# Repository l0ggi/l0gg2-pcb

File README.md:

# l0gg2-pcb
2nd gen PCB for l0ggi project

## Project
The idea behind l0ggi is to develop an open source hardware platform to log data, mainly environmental values like temperature and humidity, further also atmospheric pressure, co2, nox etc.
After a quick and dirty pcb with l0gg1 (not working out of the box) the logg2 pcb fixes all bugs of the older iteration and implements the possibility to operate the pcb via battery and accus.
l0gg2 does not feature a usb interface and is designed to be used with the open source tasmota sensors firmware (https://tasmota.github.io/docs/). As the firmware offers the possibility for OTA updates out of the box the usb interface was removed.
The type-c connector of the older iteration is replaced with a overall cheaper micro-usb. The data-lines are not terminated and not used. 

## Ordering
The gerber files are available and proven to work. 
Pick and place files are still in progress

## Firmware
While Tasmota works, the Bosch BME temperature, humidity and atmospheric pressure sensor which is intended to used with the pcb works with Tasmota-Sensors. 

### Flashing
A standard 3.3V FTDI cable can be used, but TX/RX needs to be inverted on the cable. This bug is known and will be fixed in l0gg2.1
Connect USB for power and the adapted FTDI cable to l0gg2. Press PRG (below ESP on the right) and hold and trigger RESET (below ESP on the left). Hold PRG and start flashing via the web tool of tasmota. 

### Configuration (Bosch Sensor, default)
Port | Function
---|---
GPIO0|Button 1
GPIO1|Serial TX
GPIO2|I2C SDA
GPIO3|Serial RX
GPIO4|Button 2
GPIO5|Button 3
GPIO6|
GPIO7|
GPIO8|
GPIO9|
GPIO10|
GPIO11|
GPIO12|
GPIO13|
GPIO14|I2C SCL
GPIO15|
GPIO16|
GPIO17|ADC In

### Configuration (AM2301, soldered to I2C header)
Port | Function
---|---
GPIO0|
GPIO1|
GPIO2|AM2301
GPIO3|
GPIO4|
GPIO5|
GPIO6|
GPIO7|
GPIO8|
GPIO9|
GPIO10|
GPIO11|
GPIO12|
GPIO13|
GPIO14|
GPIO15|
GPIO16|
GPIO17|

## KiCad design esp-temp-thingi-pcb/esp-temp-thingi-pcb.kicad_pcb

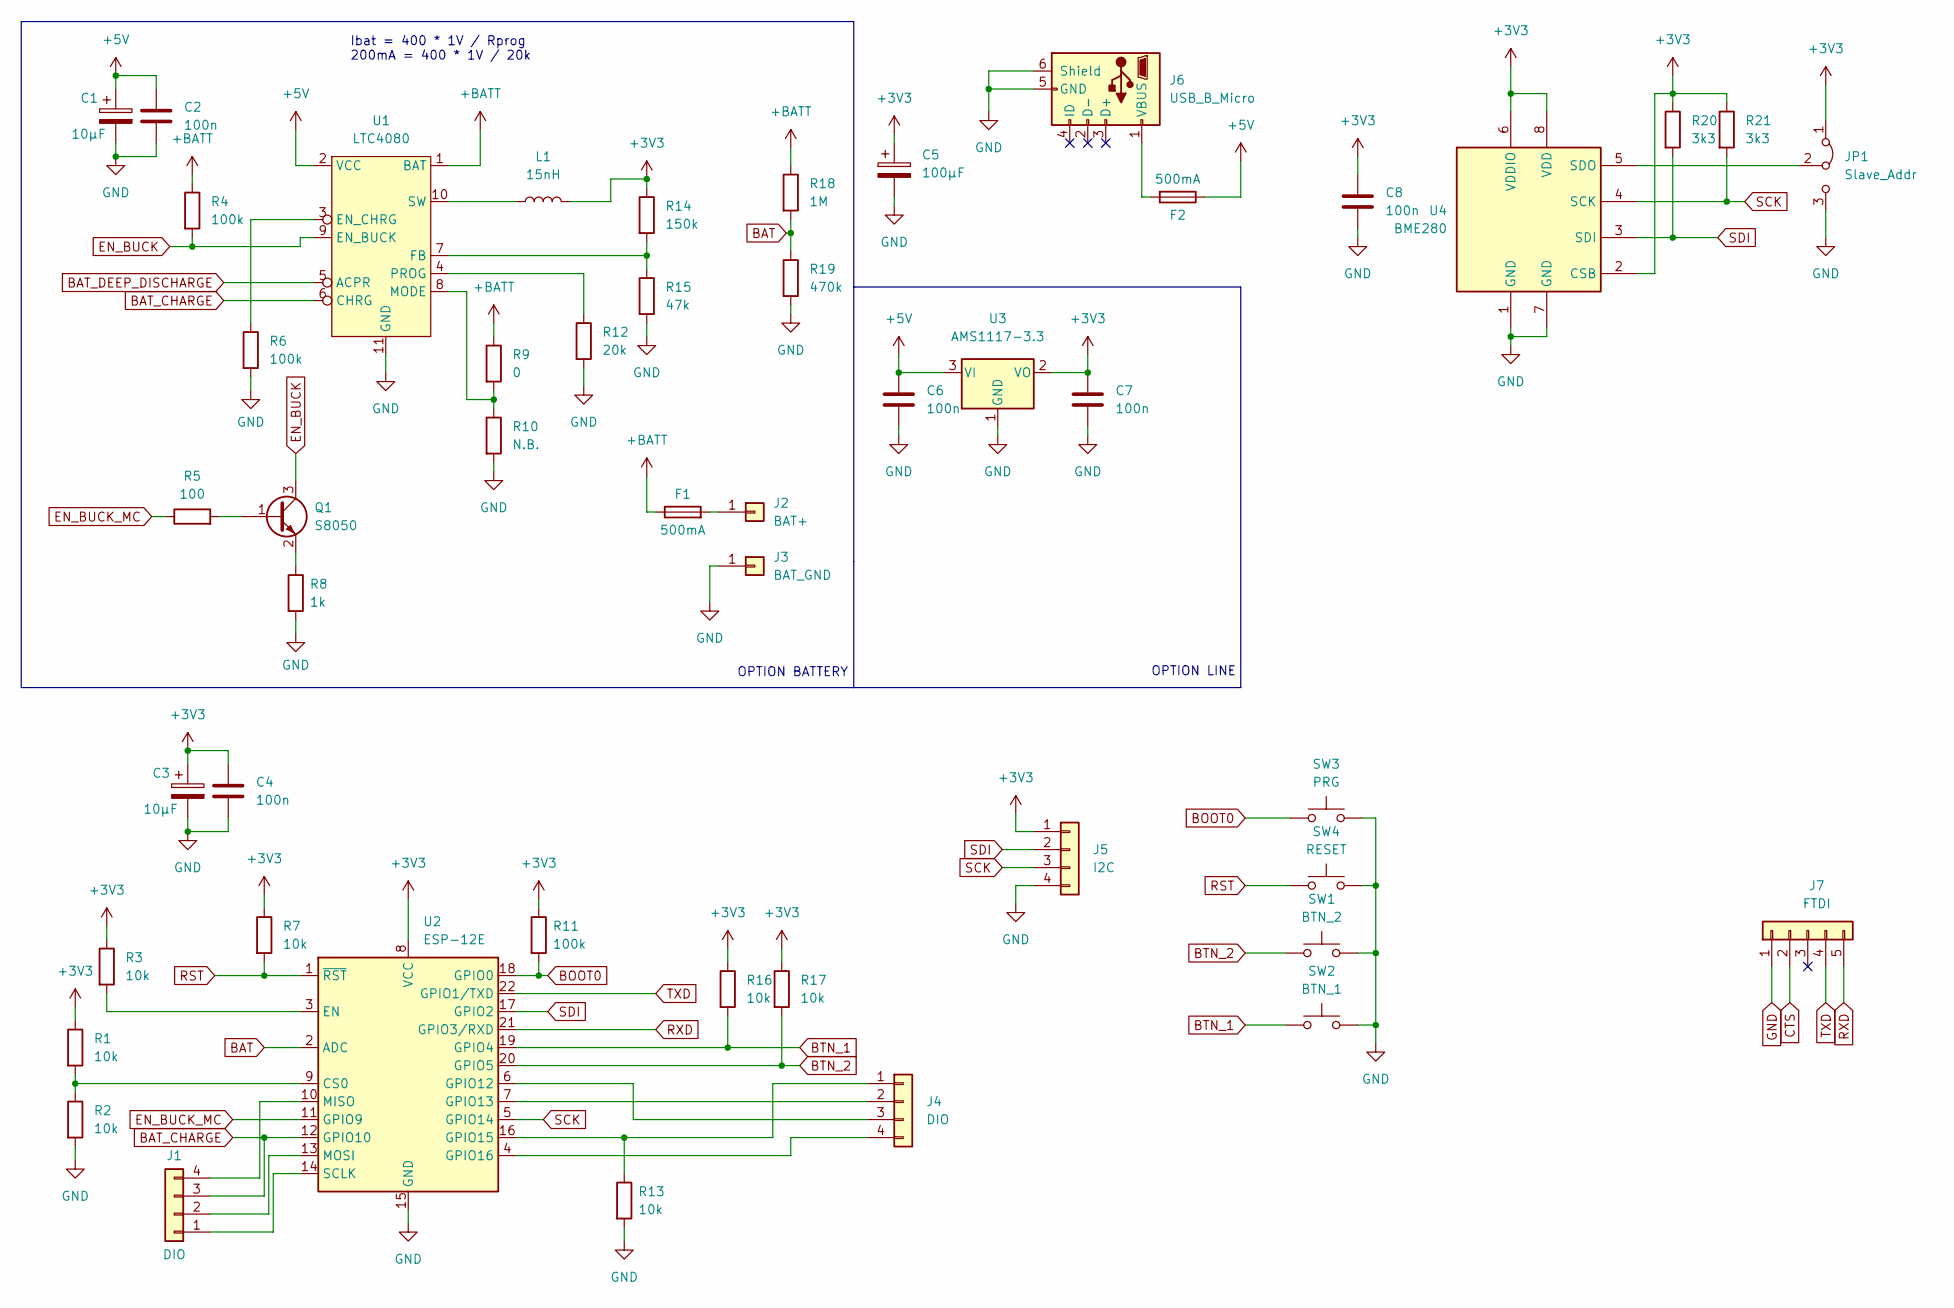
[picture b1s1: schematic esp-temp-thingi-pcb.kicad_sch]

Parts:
C1, C3: 10µF; CP_Elec_5x5.4
C2, C4, C6, C7, C8: 100n; C_0603_1608Metric
C5: 100µF; CP_Elec_5x5.4
F1, F2: 500mA; Fuse_0805_2012Metric
J1, J4: DIO; PinHeader_1x04_P2.54mm_Vertical
J2: BAT+; PinHeader_1x01_P2.54mm_Vertical
J3: BAT_GND; PinHeader_1x01_P2.54mm_Vertical
J5: I2C; PinHeader_1x04_P2.54mm_Vertical
J6: USB_B_Micro; USB_Micro-B_Amphenol_10103594-0001LF_Horizontal
J7: FTDI; PinHeader_1x05_P2.54mm_Vertical
JP1: Slave_Addr; SolderJumper-3_P1.3mm_Bridged12_Pad1.0x1.5mm
L1: 15nH; L_0603_1608Metric
Q1: S8050; SOT-23
R1, R2, R3, R7, R13, R16, R17: 10k; R_0603_1608Metric
R4, R6, R11: 100k; R_0603_1608Metric
R5: 100; R_0603_1608Metric
R8: 1k; R_0603_1608Metric
R9: 0; R_0603_1608Metric
R10: N.B.; R_0603_1608Metric
R12: 20k; R_0603_1608Metric
R14: 150k; R_0603_1608Metric
R15: 47k; R_0603_1608Metric
R18: 1M; R_0603_1608Metric
R19: 470k; R_0603_1608Metric
R20, R21: 3k3; R_0603_1608Metric
SW1: BTN_2; Panasonic_EVQPUJ_EVQPUA
SW2: BTN_1; Panasonic_EVQPUJ_EVQPUA
SW3: PRG; Panasonic_EVQPUJ_EVQPUA
SW4: RESET; Panasonic_EVQPUJ_EVQPUA
U1: LTC4080; LTC4080EMSE-PBF
U2: ESP-12E
U3: AMS1117-3.3; SOT-223-3_TabPin2
U4: BME280; Bosch_LGA-8_2.5x2.5mm_P0.65mm_ClockwisePinNumbering

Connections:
+3V3: C3.1, C4.1, C5.1, C7.1, C8.1, J5.1, JP1.1 (A), L1.2, R1.1, R3.1, R7.1, R11.1, R14.1, R16.1, R17.1, R20.1, R21.1, U2.8 (VCC), U3.2 (VO), U4.2 (CSB), U4.6 (VDDIO), U4.8 (VDD)
+BATT: F1.1, R4.1, R9.1, R18.1, U1.1 (BAT)
BAT: R18.2, R19.1, U2.2 (ADC)
BAT_CHARGE: J1.3, U1.6 (CHRG), U2.12 (GPIO10)
BAT_DEEP_DISCHARGE: U1.5 (ACPR)
BOOT0: R11.2, SW3.1, U2.18 (GPIO0)
BTN_1: R16.2, SW2.1, U2.19 (GPIO4)
BTN_2: R17.2, SW1.1, U2.20 (GPIO5)
CTS: J7.2
EN_BUCK: Q1.3 (C), R4.2, U1.9 (EN_BUCK)
EN_BUCK_MC: R5.1, U2.11 (GPIO9)
GND: C1.2, C2.2, C3.2, C4.2, C5.2, C6.2, C7.2, C8.2, J3.1, J5.4, J6.5 (GND), J6.6 (Shield), J7.1, JP1.3 (B), R2.2, R8.2, R10.2, R12.2, R13.2, R15.2, R19.2, SW1.2, SW2.2, SW3.2, SW4.2, U1.11 (GND), U2.15 (GND), U3.1 (GND), U4.1 (GND), U4.7 (GND)
unnamed: F1.2, J2.1
unnamed: F2.2, J6.1 (VBUS)
unnamed: J1.1, U2.14 (SCLK)
unnamed: J1.2, U2.13 (MOSI)
unnamed: J1.4, U2.10 (MISO)
unnamed: J4.1, R13.1, U2.16 (GPIO15)
unnamed: J4.2, U2.7 (GPIO13)
unnamed: J4.3, U2.6 (GPIO12)
unnamed: J4.4, U2.4 (GPIO16)
unnamed: JP1.2 (C), U4.5 (SDO)
unnamed: L1.1, U1.10 (SW)
unnamed: Q1.1 (B), R5.2
unnamed: Q1.2 (E), R8.1
unnamed: R1.2, R2.1, U2.9 (CS0)
unnamed: R3.2, U2.3 (EN)
unnamed: R9.2, R10.1, U1.8 (MODE)
unnamed: R12.1, U1.4 (PROG)
unnamed: R14.2, R15.1, U1.7 (FB)
RST: R7.2, SW4.1, U2.1 (~RST)
RXD: J7.5, U2.21 (GPIO3/RXD)
SCK: J5.3, R21.2, U2.5 (GPIO14), U4.4 (SCK)
SDI: J5.2, R20.2, U2.17 (GPIO2), U4.3 (SDI)
TXD: J7.4, U2.22 (GPIO1/TXD)

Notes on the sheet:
OPTION BATTERY
Ibat = 400 * 1V / Rprog 200mA = 400 * 1V / 20k
OPTION LINE

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
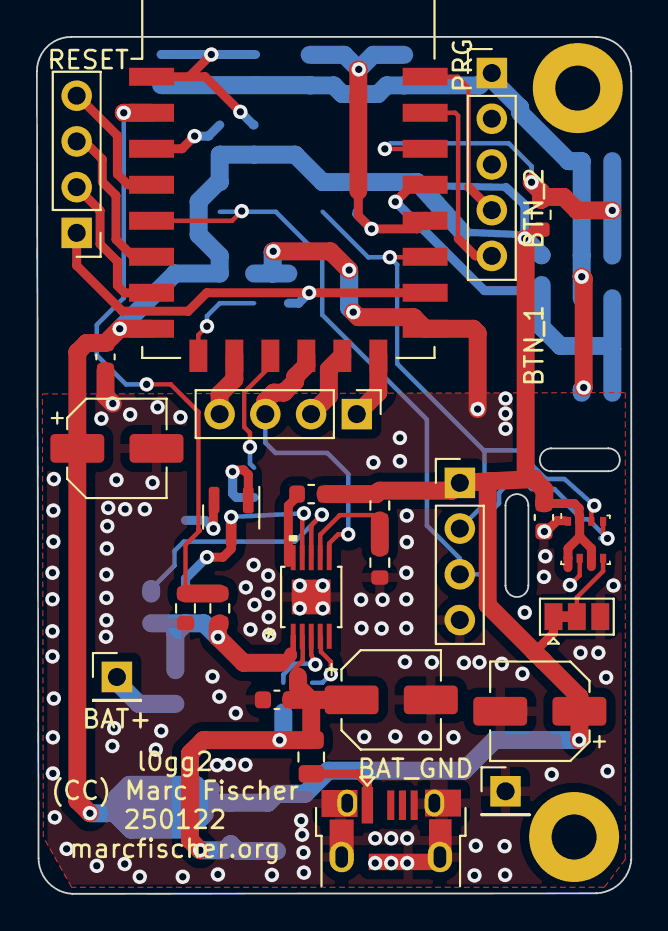
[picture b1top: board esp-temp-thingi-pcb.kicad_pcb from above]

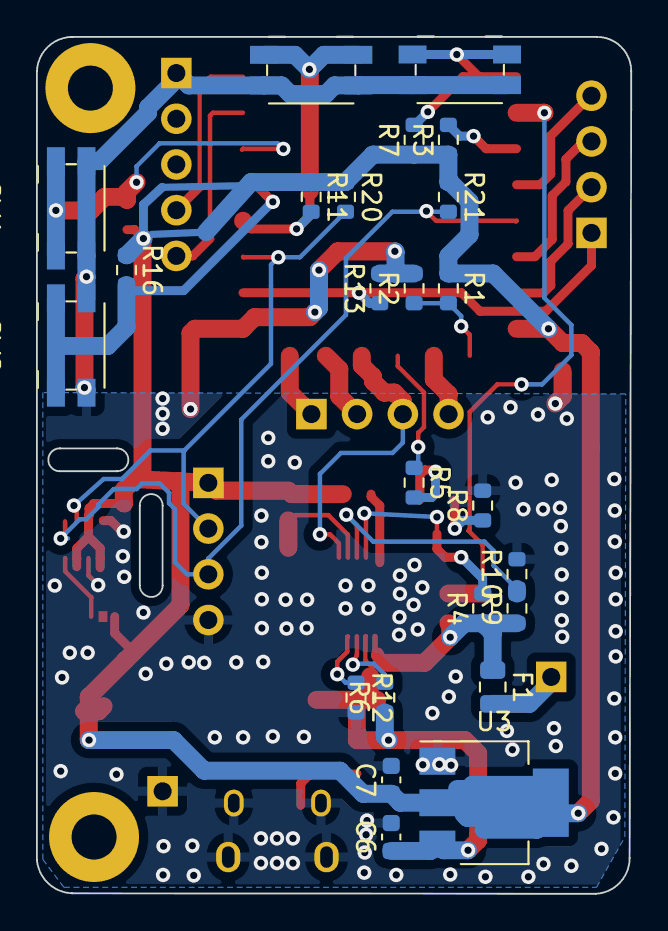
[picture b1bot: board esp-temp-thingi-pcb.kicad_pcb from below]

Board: 2 copper layers, 33.0 x 47.6 mm, 49 parts (24 on the bottom side), 35 nets.

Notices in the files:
parts and their libraries:
Copyright 2021 Accelerated Designs. All rights reserved.
